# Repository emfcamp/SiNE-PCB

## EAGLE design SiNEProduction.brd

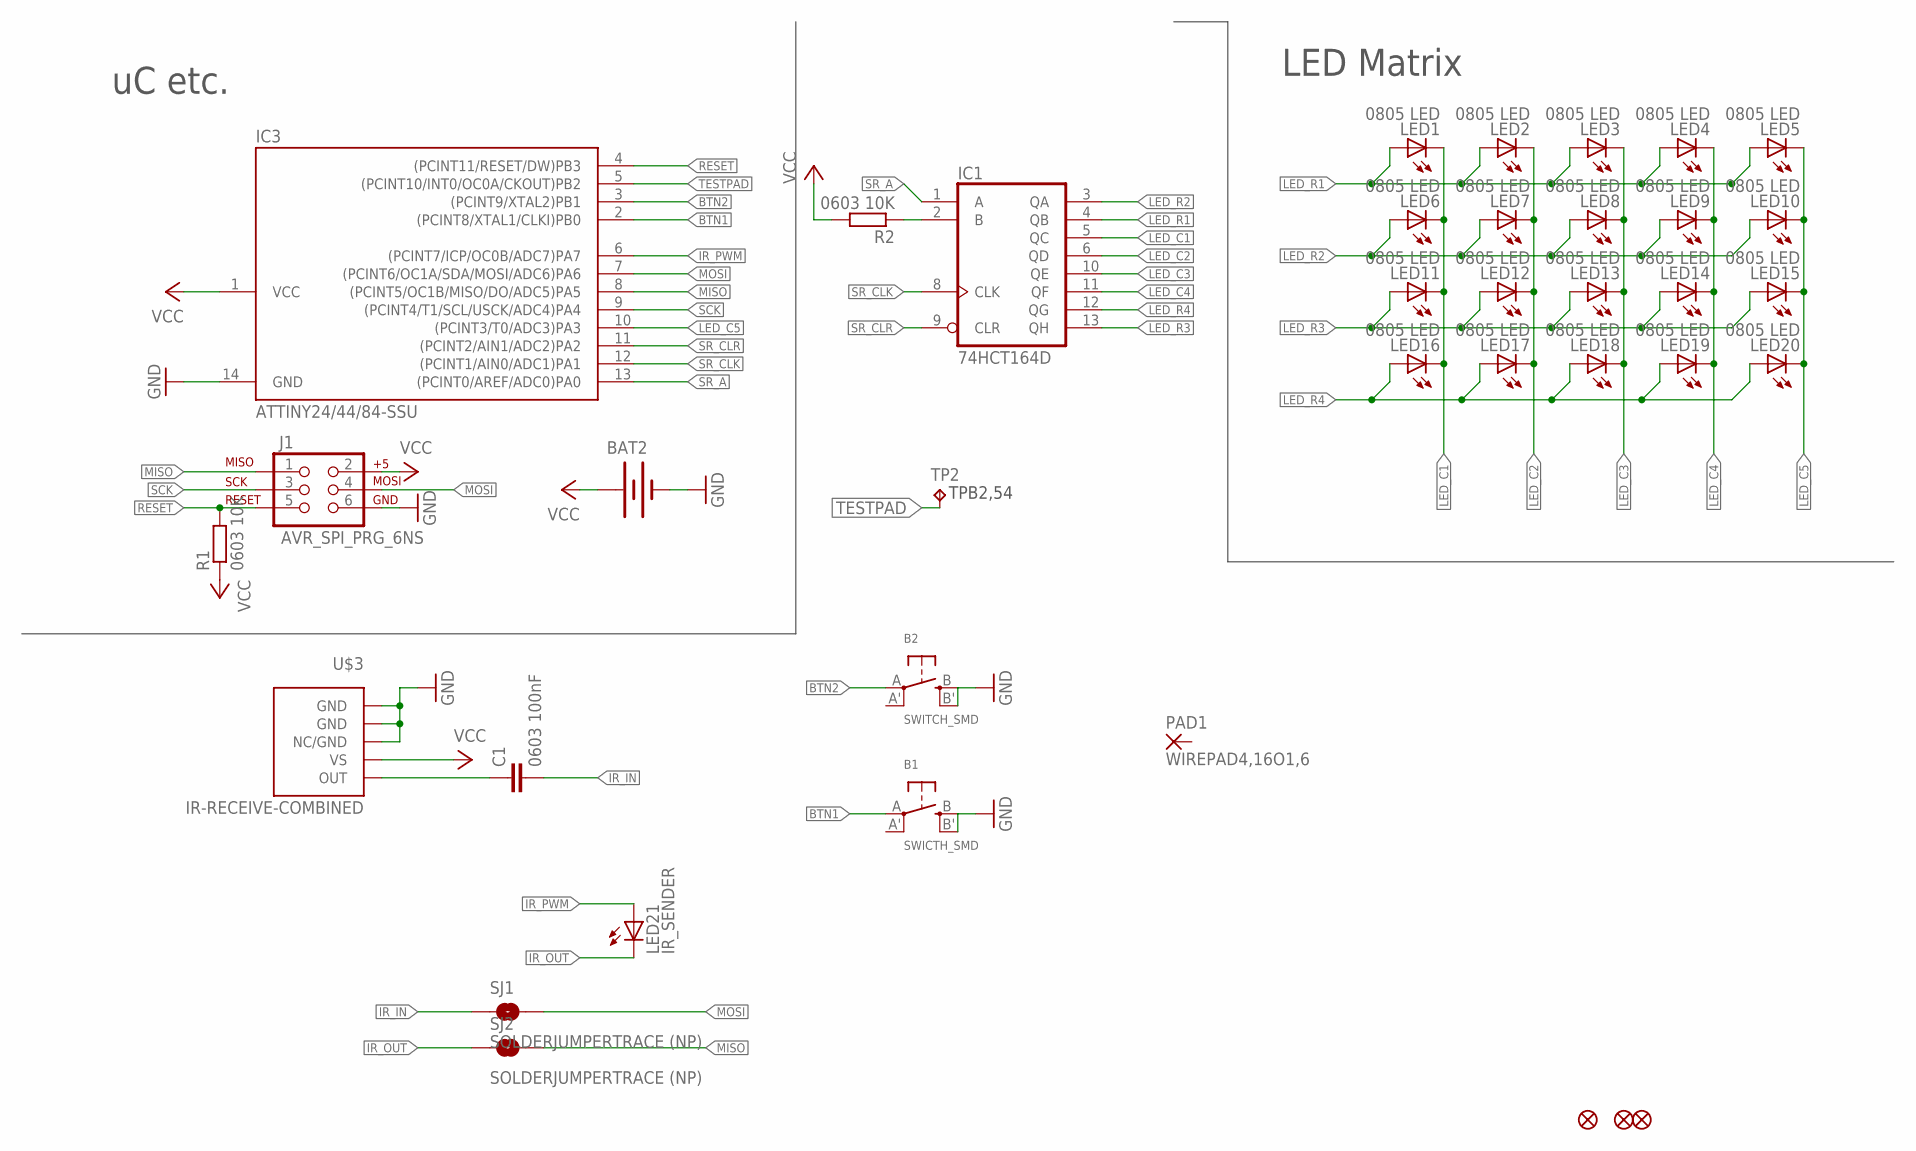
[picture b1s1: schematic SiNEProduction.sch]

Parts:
B1: SWICTH_SMD; EVQ-Q2
B2: SWITCH_SMD; EVQ-Q2
BAT2: BATTERY20SMD; BATTCON_20MM
C1: 0603 100nF; C0805
IC1: 74HCT164D; SO14
IC3: ATTINY24/44/84-SSU; SOIC14
J1: AVR_SPI_PRG_6NS; 2X3-NS
JP1, JP2, JP3: FIDUCIAL1X2.5-STOP; FIDUCIAL-1X2.5-STOP
LED1, LED2, LED3, LED4, LED5, LED6, LED7, LED8, LED9, LED10, LED11, LED12, LED13, LED14, LED15, LED16, LED17, LED18, LED19, LED20: 0805 LED; CHIPLED_0805
LED21: IR_SENDER; CHIPLED_1206
PAD1: WIREPAD4,16O1,6; 4,16O1,6
R1, R2: 0603 10K; R0805
SJ1, SJ2: SOLDERJUMPERTRACE (NP); SJ_2S-TRACE
TP2: TPB2,54; B2,54
U$3: IR-RECEIVE-COMBINED; TSOP-COMBINED

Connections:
BTN1: B1.A, IC3.2 ((PCINT8/XTAL1/CLKI)PB0)
BTN2: B2.A, IC3.3 ((PCINT9/XTAL2)PB1)
GND: B1.B (S), B1.B' (S1), B2.B (S), B2.B' (S1), BAT2.2 (-), IC1.7 (GND), IC3.14 (GND), J1.6, U$3.1 (GND), U$3.2 (NC/GND), U$3.5 (GND)
IR_IN: C1.2, SJ1.1
IR_OUT: LED21.C, SJ2.1
IR_PWM: IC3.6 ((PCINT7/ICP/OC0B/ADC7)PA7), LED21.A
LED_C1: IC1.5 (QC), LED1.C, LED6.C, LED11.C, LED16.C
LED_C2: IC1.6 (QD), LED2.C, LED7.C, LED12.C, LED17.C
LED_C3: IC1.10 (QE), LED3.C, LED8.C, LED13.C, LED18.C
LED_C4: IC1.11 (QF), LED4.C, LED9.C, LED14.C, LED19.C
LED_C5: IC3.10 ((PCINT3/T0/ADC3)PA3), LED5.C, LED10.C, LED15.C, LED20.C
LED_R1: IC1.4 (QB), LED1.A, LED2.A, LED3.A, LED4.A, LED5.A
LED_R2: IC1.3 (QA), LED6.A, LED7.A, LED8.A, LED9.A, LED10.A
LED_R3: IC1.13 (QH), LED11.A, LED12.A, LED13.A, LED14.A, LED15.A
LED_R4: IC1.12 (QG), LED16.A, LED17.A, LED18.A, LED19.A, LED20.A
MISO: IC3.8 ((PCINT5/OC1B/MISO/DO/ADC5)PA5), J1.1, SJ2.2
MOSI: IC3.7 ((PCINT6/OC1A/SDA/MOSI/ADC6)PA6), J1.4, SJ1.2
unnamed: IC1.2 (B), R2.1
unnamed: C1.1, U$3.4 (OUT)
RESET: IC3.4 ((PCINT11/RESET/DW)PB3), J1.5, R1.2
SCK: IC3.9 ((PCINT4/T1/SCL/USCK/ADC4)PA4), J1.3
SR_A: IC1.1 (A), IC3.13 ((PCINT0/AREF/ADC0)PA0)
SR_CLK: IC1.8 (CLK), IC3.12 ((PCINT1/AIN0/ADC1)PA1)
SR_CLR: IC1.9 (CLR), IC3.11 ((PCINT2/AIN1/ADC2)PA2)
TESTPAD: IC3.5 ((PCINT10/INT0/OC0A/CKOUT)PB2), TP2.TP
VCC: BAT2.1 (+), IC1.14 (VCC), IC3.1 (VCC), J1.2, R1.1, R2.2, U$3.3 (VS)

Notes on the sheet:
LED Matrix
uC etc.

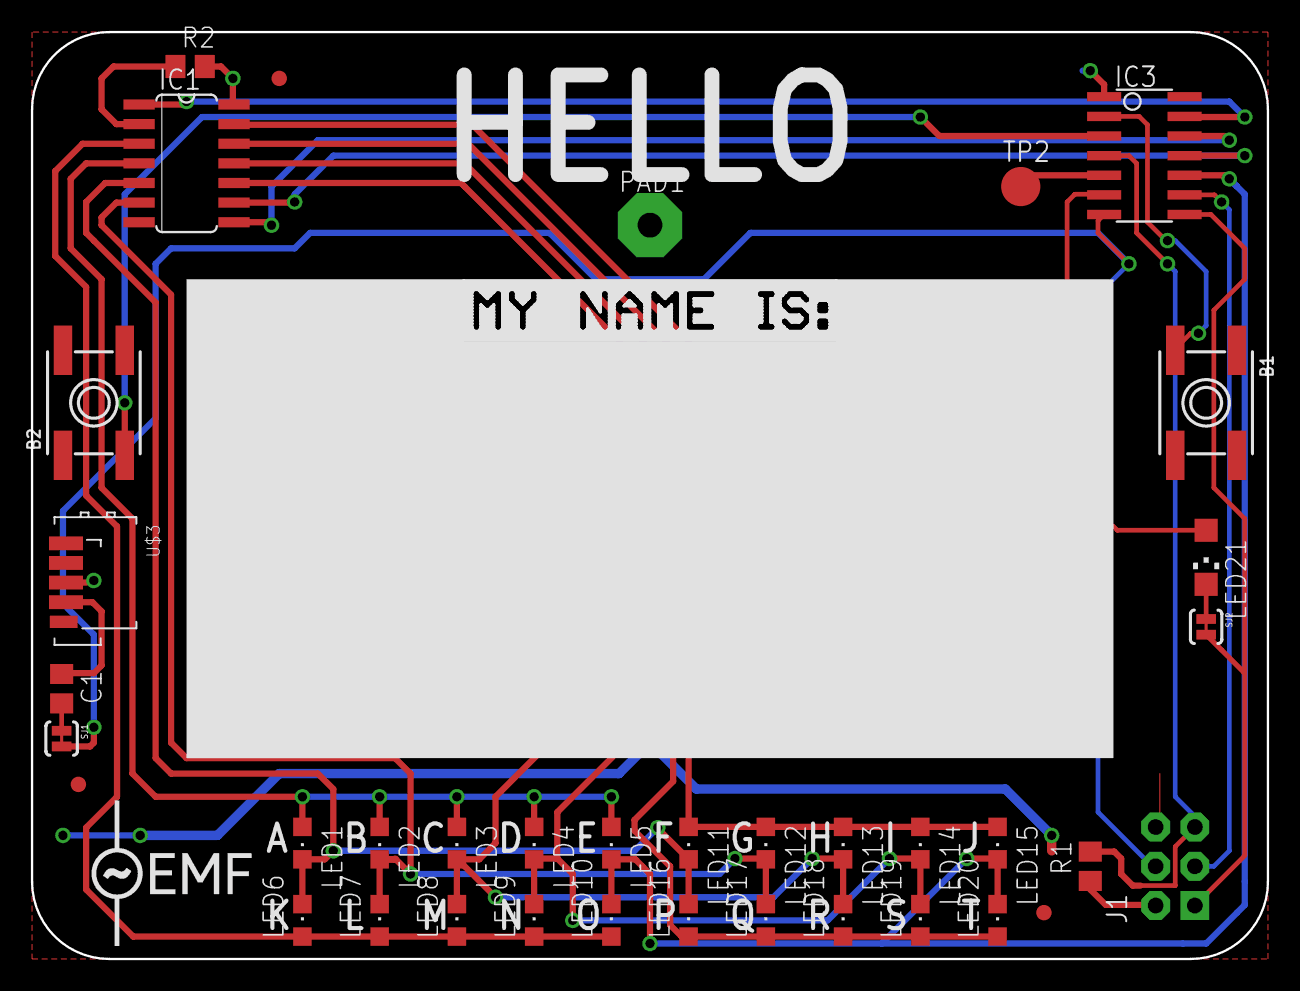
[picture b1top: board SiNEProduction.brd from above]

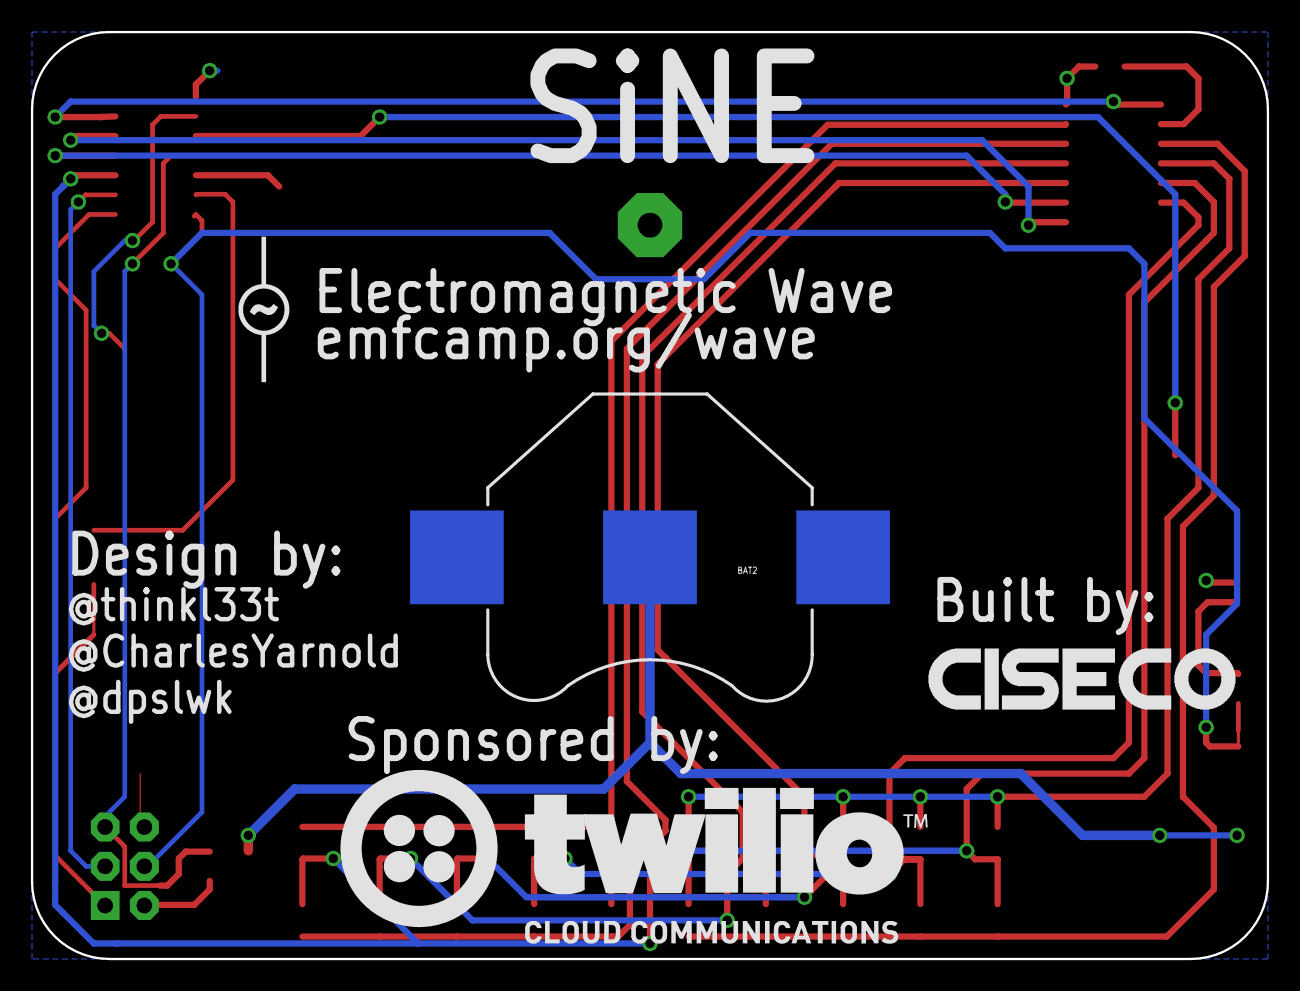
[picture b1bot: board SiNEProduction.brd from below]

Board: 2 copper layers, 80.0 x 60.0 mm, 43 parts (4 on the bottom side), 26 nets.

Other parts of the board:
U$1: TWILIO
U$2: EMFLOGO1
U$4: NAME
U$5: CISECO1
U$6: EMFLOGO

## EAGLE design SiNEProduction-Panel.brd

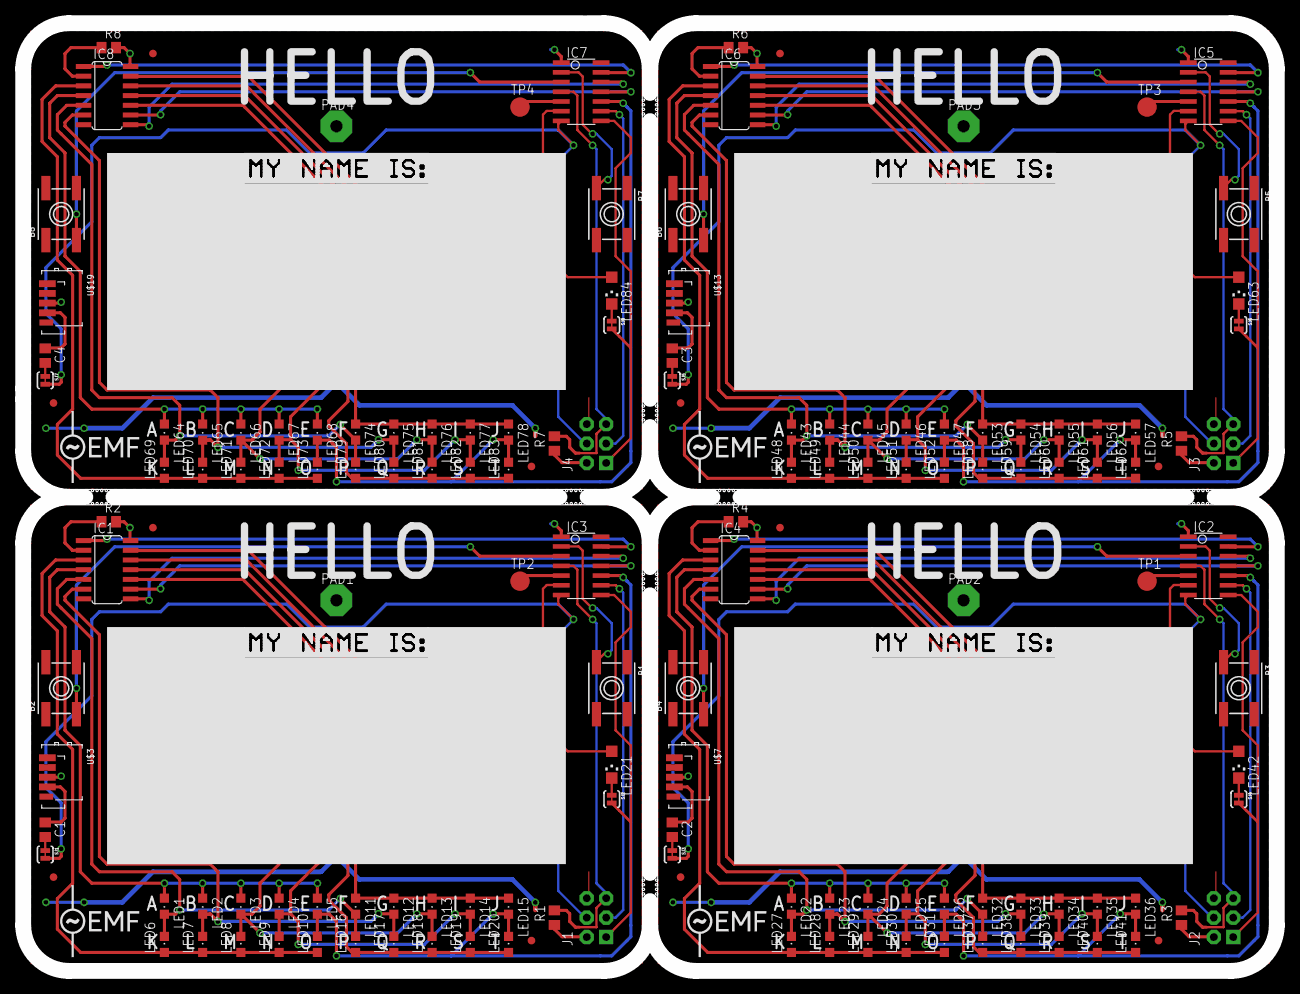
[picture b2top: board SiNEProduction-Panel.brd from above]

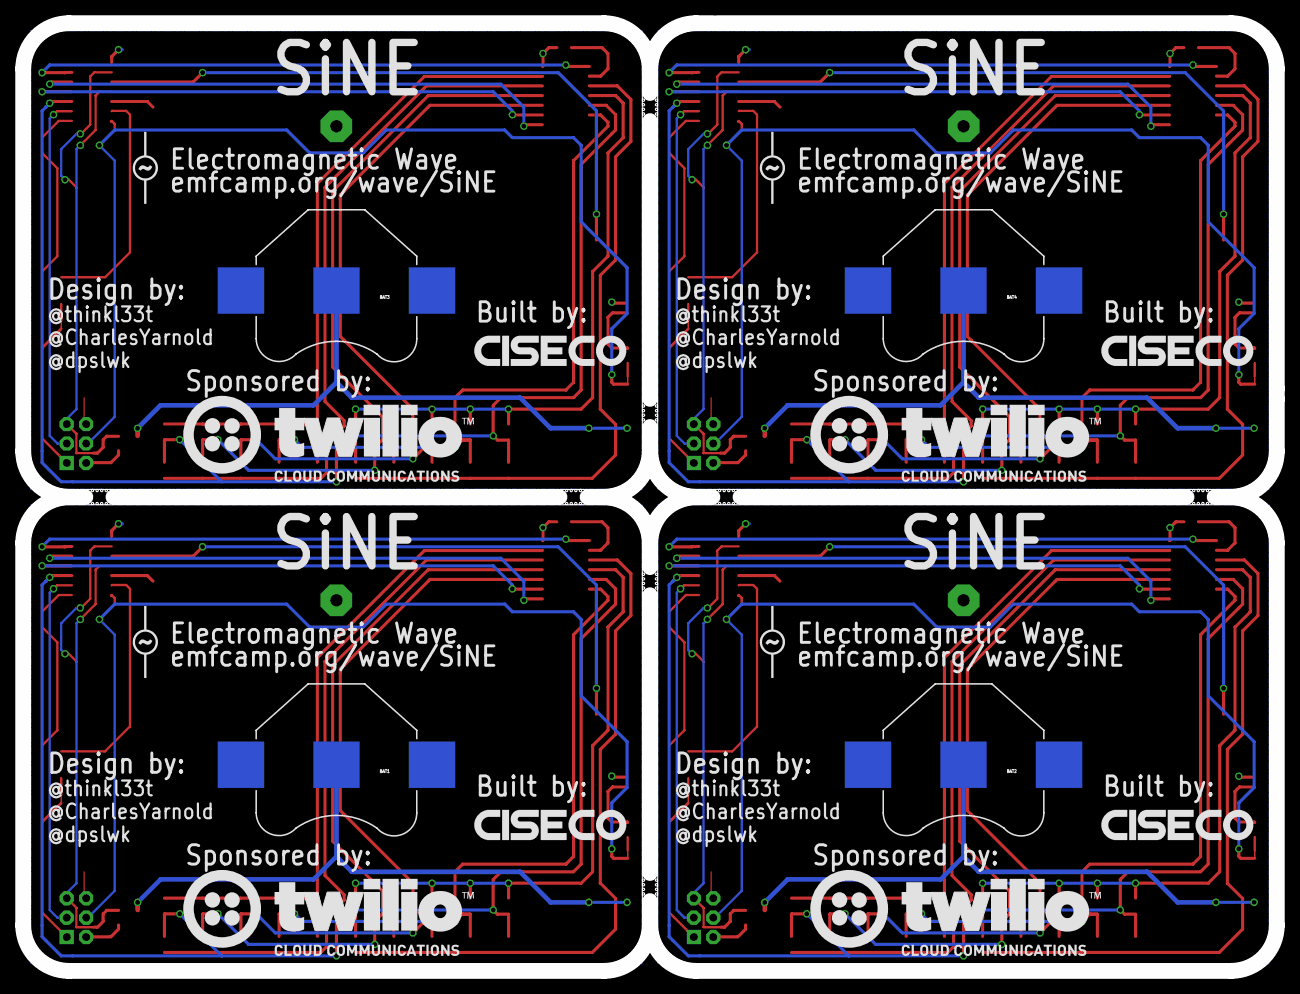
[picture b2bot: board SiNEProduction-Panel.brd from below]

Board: 2 copper layers, 164.0 x 124.0 mm, 172 parts (16 on the bottom side), 104 nets.

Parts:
B1, B3, B5, B7: SWICTH_SMD; EVQ-Q2
B2, B4, B6, B8: SWITCH_SMD; EVQ-Q2
BAT1, BAT2, BAT3, BAT4: BATTCON_20MM
C1, C2, C3, C4: 0603 100nF; C0805
IC1, IC4, IC6, IC8: 74HCT164D; SO14
IC2, IC3, IC5, IC7: ATTINY24/44/84-SSU; SOIC14
J1, J2, J3, J4: AVR_SPI_PRG_6NS; 2X3-NS
JP1, JP2, JP3, JP4, JP5, JP6, JP7, JP8, JP9, JP10, JP11, JP12: FIDUCIAL1X2.5-STOP; FIDUCIAL-1X2.5-STOP
LED1, LED2, LED3, LED4, LED5, LED6, LED7, LED8, LED9, LED10, LED11, LED12, LED13, LED14, LED15, LED16, LED17, LED18, LED19, LED20, LED22, LED23, LED24, LED25, LED26, LED27, LED28, LED29, LED30, LED31, LED32, LED33, LED34, LED35, LED36, LED37, LED38, LED39, LED40, LED41, LED43, LED44, LED45, LED46, LED47, LED48, LED49, LED50, LED51, LED52, LED53, LED54, LED55, LED56, LED57, LED58, LED59, LED60, LED61, LED62, LED64, LED65, LED66, LED67, LED68, LED69, LED70, LED71, LED72, LED73, LED74, LED75, LED76, LED77, LED78, LED79, LED80, LED81, LED82, LED83: 0805 LED; CHIPLED_0805
LED21, LED42, LED63, LED84: IR_SENDER; CHIPLED_1206
PAD1, PAD2, PAD3, PAD4: WIREPAD4,16O1,6; 4,16O1,6
R1, R2, R3, R4, R5, R6, R7, R8: 0603 10K; R0805
SJ1, SJ2, SJ3, SJ4, SJ5, SJ6, SJ7, SJ8: SOLDERJUMPERTRACE (NP); SJ_2S-TRACE
TP1, TP2, TP3, TP4: TPB2,54; B2,54
U$1, U$8, U$14, U$20: TWILIO
U$2, U$12, U$18, U$24: EMFLOGO1
U$3, U$7, U$13, U$19: IR-RECEIVE-COMBINED; TSOP-COMBINED
U$4, U$10, U$16, U$22: NAME
U$5, U$9, U$15, U$21: CISECO1
U$6, U$11, U$17, U$23: EMFLOGO

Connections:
BTN1: B1.A, IC3.2
BTN2: B2.A, IC3.3
BTN3: B4.A, IC2.3
BTN4: B3.A, IC2.2
BTN5: B6.A, IC5.3
BTN6: B5.A, IC5.2
BTN7: B8.A, IC7.3
BTN8: B7.A, IC7.2
GND: B1.B, B1.B', B2.B, B2.B', BAT2.2, IC1.7, IC3.14, J1.6, U$3.1, U$3.2, U$3.5
GND1: B3.B, B3.B', B4.B, B4.B', BAT1.2, IC2.14, IC4.7, J2.6, U$7.1, U$7.2, U$7.5
GND2: B5.B, B5.B', B6.B, B6.B', BAT3.2, IC5.14, IC6.7, J3.6, U$13.1, U$13.2, U$13.5
GND3: B7.B, B7.B', B8.B, B8.B', BAT4.2, IC7.14, IC8.7, J4.6, U$19.1, U$19.2, U$19.5
IR_IN: C1.2, SJ1.1
IR_IN1: C2.2, SJ3.1
IR_IN2: C3.2, SJ5.1
IR_IN3: C4.2, SJ7.1
IR_OUT: LED21.C, SJ2.1
IR_OUT1: LED42.C, SJ4.1
IR_OUT2: LED63.C, SJ6.1
IR_OUT3: LED84.C, SJ8.1
IR_PWM: IC3.6, LED21.A
IR_PWM1: IC2.6, LED42.A
IR_PWM2: IC5.6, LED63.A
IR_PWM3: IC7.6, LED84.A
LED_C1: IC1.5, LED1.C, LED6.C, LED11.C, LED16.C
LED_C2: IC1.6, LED2.C, LED7.C, LED12.C, LED17.C
LED_C3: IC1.10, LED3.C, LED8.C, LED13.C, LED18.C
LED_C4: IC1.11, LED4.C, LED9.C, LED14.C, LED19.C
LED_C5: IC3.10, LED5.C, LED10.C, LED15.C, LED20.C
LED_C6: IC4.6, LED23.C, LED28.C, LED33.C, LED38.C
LED_C7: IC2.10, LED26.C, LED31.C, LED36.C, LED41.C
LED_C8: IC4.10, LED24.C, LED29.C, LED34.C, LED39.C
LED_C9: IC4.11, LED25.C, LED30.C, LED35.C, LED40.C
LED_C10: IC4.5, LED22.C, LED27.C, LED32.C, LED37.C
LED_C11: IC6.6, LED44.C, LED49.C, LED54.C, LED59.C
LED_C12: IC5.10, LED47.C, LED52.C, LED57.C, LED62.C
LED_C13: IC6.10, LED45.C, LED50.C, LED55.C, LED60.C
LED_C14: IC6.11, LED46.C, LED51.C, LED56.C, LED61.C
LED_C15: IC6.5, LED43.C, LED48.C, LED53.C, LED58.C
LED_C16: IC8.6, LED65.C, LED70.C, LED75.C, LED80.C
LED_C17: IC7.10, LED68.C, LED73.C, LED78.C, LED83.C
LED_C18: IC8.10, LED66.C, LED71.C, LED76.C, LED81.C
LED_C19: IC8.11, LED67.C, LED72.C, LED77.C, LED82.C
LED_C20: IC8.5, LED64.C, LED69.C, LED74.C, LED79.C
LED_R1: IC1.4, LED1.A, LED2.A, LED3.A, LED4.A, LED5.A
LED_R2: IC1.3, LED6.A, LED7.A, LED8.A, LED9.A, LED10.A
LED_R3: IC1.13, LED11.A, LED12.A, LED13.A, LED14.A, LED15.A
LED_R4: IC1.12, LED16.A, LED17.A, LED18.A, LED19.A, LED20.A
LED_R5: IC4.4, LED22.A, LED23.A, LED24.A, LED25.A, LED26.A
LED_R6: IC4.3, LED27.A, LED28.A, LED29.A, LED30.A, LED31.A
LED_R7: IC4.13, LED32.A, LED33.A, LED34.A, LED35.A, LED36.A
LED_R8: IC4.12, LED37.A, LED38.A, LED39.A, LED40.A, LED41.A
LED_R9: IC6.4, LED43.A, LED44.A, LED45.A, LED46.A, LED47.A
LED_R10: IC6.3, LED48.A, LED49.A, LED50.A, LED51.A, LED52.A
LED_R11: IC6.13, LED53.A, LED54.A, LED55.A, LED56.A, LED57.A
LED_R12: IC6.12, LED58.A, LED59.A, LED60.A, LED61.A, LED62.A
LED_R13: IC8.4, LED64.A, LED65.A, LED66.A, LED67.A, LED68.A
LED_R14: IC8.3, LED69.A, LED70.A, LED71.A, LED72.A, LED73.A
LED_R15: IC8.13, LED74.A, LED75.A, LED76.A, LED77.A, LED78.A
LED_R16: IC8.12, LED79.A, LED80.A, LED81.A, LED82.A, LED83.A
MISO: IC3.8, J1.1, SJ2.2
MISO1: IC2.8, J2.1, SJ4.2
MISO2: IC5.8, J3.1, SJ6.2
MISO3: IC7.8, J4.1, SJ8.2
MOSI: IC3.7, J1.4, SJ1.2
MOSI1: IC2.7, J2.4, SJ3.2
MOSI2: IC5.7, J3.4, SJ5.2
MOSI3: IC7.7, J4.4, SJ7.2
unnamed: IC1.2, R2.1
unnamed: IC4.2, R4.1
unnamed: C2.1, U$7.4
unnamed: IC6.2, R6.1
unnamed: C3.1, U$13.4
unnamed: C1.1, U$3.4
unnamed: IC8.2, R8.1
unnamed: C4.1, U$19.4
RESET: IC3.4, J1.5, R1.2
RESET1: IC2.4, J2.5, R3.2
RESET2: IC5.4, J3.5, R5.2
RESET3: IC7.4, J4.5, R7.2
SCK: IC3.9, J1.3
SCK1: IC2.9, J2.3
SCK2: IC5.9, J3.3
SCK3: IC7.9, J4.3
SR_A: IC1.1, IC3.13
SR_A1: IC2.13, IC4.1
SR_A2: IC5.13, IC6.1
SR_A3: IC7.13, IC8.1
SR_CLK: IC1.8, IC3.12
SR_CLK1: IC2.12, IC4.8
SR_CLK2: IC5.12, IC6.8
SR_CLK3: IC7.12, IC8.8
SR_CLR: IC1.9, IC3.11
SR_CLR1: IC2.11, IC4.9
SR_CLR2: IC5.11, IC6.9
SR_CLR3: IC7.11, IC8.9
TESTPAD: IC3.5, TP2.TP
TESTPAD1: IC2.5, TP1.TP
TESTPAD2: IC5.5, TP3.TP
TESTPAD3: IC7.5, TP4.TP
VCC: BAT2.1, IC1.14, IC3.1, J1.2, R1.1, R2.2, U$3.3
VCC1: BAT1.1, IC2.1, IC4.14, J2.2, R3.1, R4.2, U$7.3
VCC2: BAT3.1, IC5.1, IC6.14, J3.2, R5.1, R6.2, U$13.3
VCC3: BAT4.1, IC7.1, IC8.14, J4.2, R7.1, R8.2, U$19.3

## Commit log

2013-03-04 added v0.1 SiNE Board
2013-03-04 Added temp files to gitignore
2013-03-05 Added SiNE Part library with ATTiny, IR Receiver and Mouser SMD Tach switch footprints
2013-03-15 DevBoard v0.2
2013-03-15 DevBoard V0.3
2013-03-15 DevBoard V0.4
2013-03-15 DevBoard V0.5 Final Changes including Teardrops, this version was sent to make 3 prototype boards
2013-03-15 Added parts use in DevBoard v0.5 to the lbr Update parts in the DevBoard to use versions from the lbr DevBoard V0.5a
2013-03-15 Adding IR- Sender part to lbr Farnell part 9707816 Sharp GL100MD1MP1
2013-03-25 First commit of production
2013-03-25 Moved Battery clip up a little, added bRestrict for better contact Fixed trace width in lower right corner
2013-03-29 Added TSOP75X version of the IR receiver and a combine part that will cover both parts if we need
2013-03-29 Updated to use the combined IR Receiver footprint in case we have to switch parts
2013-04-07 Changed font to Vector
2013-04-07 Swapped sides for one button and IR Receiver Added bottom silk screen Added posible holle for Pin
2013-04-09 Adding Logo's
2013-04-09 Inverted MY NAME IS:
2013-04-09 Labeled LED's
2013-04-09 Adding Fiducials
2013-04-09 Last trace tweaks
2013-04-09 Adding Gerbers
2013-04-10 Last tweaks for EMF Logo
2013-04-19 Adding panel version

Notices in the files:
parts and their libraries:
microbuilder: This work is placed in the public domain, and may be freely used for commercial and non-commercial work with the following conditions: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
SparkFun: Licensing: CC v3.0 Share-Alike You are welcome to use this library for commercial purposes.
